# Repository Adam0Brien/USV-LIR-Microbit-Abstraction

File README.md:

# USV-LIR-Microbit-Abstraction
Final year project Applied Computing (IoT)

## Academic Title - "USV-Lir Micro: bit Sensor Pod Abstraction"

## Commercial Title - "Micro:Bit Sensor Pod breakout Board"
<br>

<br>

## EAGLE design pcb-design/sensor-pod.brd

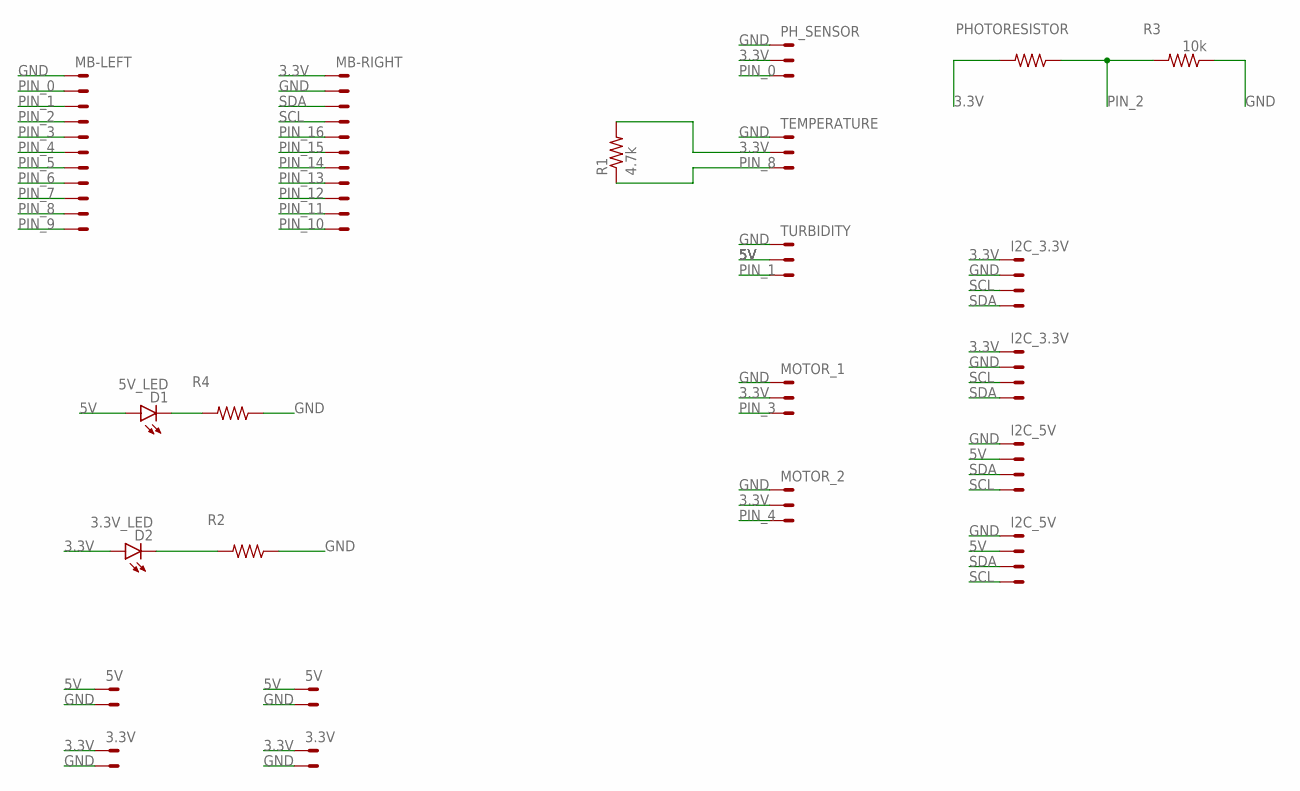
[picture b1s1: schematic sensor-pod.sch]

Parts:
1: 5V; 22-23-2021
D1: 5V_LED; SFH482
D2: 3.3V_LED; SFH482
PHOTORESISTOR: R-US_0204/7; 0204/7
R1: 4.7k; 0204/7
R2, R4: R-US_0204/7; 0204/7
R3: 10k; 0204/7
X1: PH_SENSOR; 22-23-2031
X2, X10: I2C_5V; 22-23-2041
X3: TURBIDITY; 22-23-2031
X4: 5V; 22-23-2021
X5: TEMPERATURE; 22-23-2031
X6: MOTOR_1; 22-23-2031
X7: MOTOR_2; 22-23-2031
X8, X9: I2C_3.3V; 22-23-2041
X11, X12: 3.3V; 22-23-2021
X15: MB-LEFT; 22-23-2111
X16: MB-RIGHT; 22-23-2111

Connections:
3.3V: D2.A, PHOTORESISTOR.2, R1.2, X1.2, X5.2, X6.2, X7.2, X8.1, X9.1, X11.1, X12.1, X16.1
5V: 1.1, D1.A, X2.2, X3.2, X4.1, X10.2
GND: 1.2, R2.1, R3.1, R4.1, X1.1, X2.1, X3.1, X4.2, X5.1, X6.1, X7.1, X8.2, X9.2, X10.1, X11.2, X12.2, X15.1, X16.2
unnamed: D1.K (C), R4.2
unnamed: D2.K (C), R2.2
PIN_0: X1.3, X15.2
PIN_1: X3.3, X15.3
PIN_2: PHOTORESISTOR.1, R3.2, X15.4
PIN_3: X6.3, X15.5
PIN_4: X7.3, X15.6
PIN_5: X15.7
PIN_6: X15.8
PIN_7: X15.9
PIN_8: R1.1, X5.3, X15.10
PIN_9: X15.11
PIN_10: X16.11
PIN_11: X16.10
PIN_12: X16.9
PIN_13: X16.8
PIN_14: X16.7
PIN_15: X16.6
PIN_16: X16.5
SCL: X2.4, X8.3, X9.3, X10.4, X16.4
SDA: X2.3, X8.4, X9.4, X10.3, X16.3

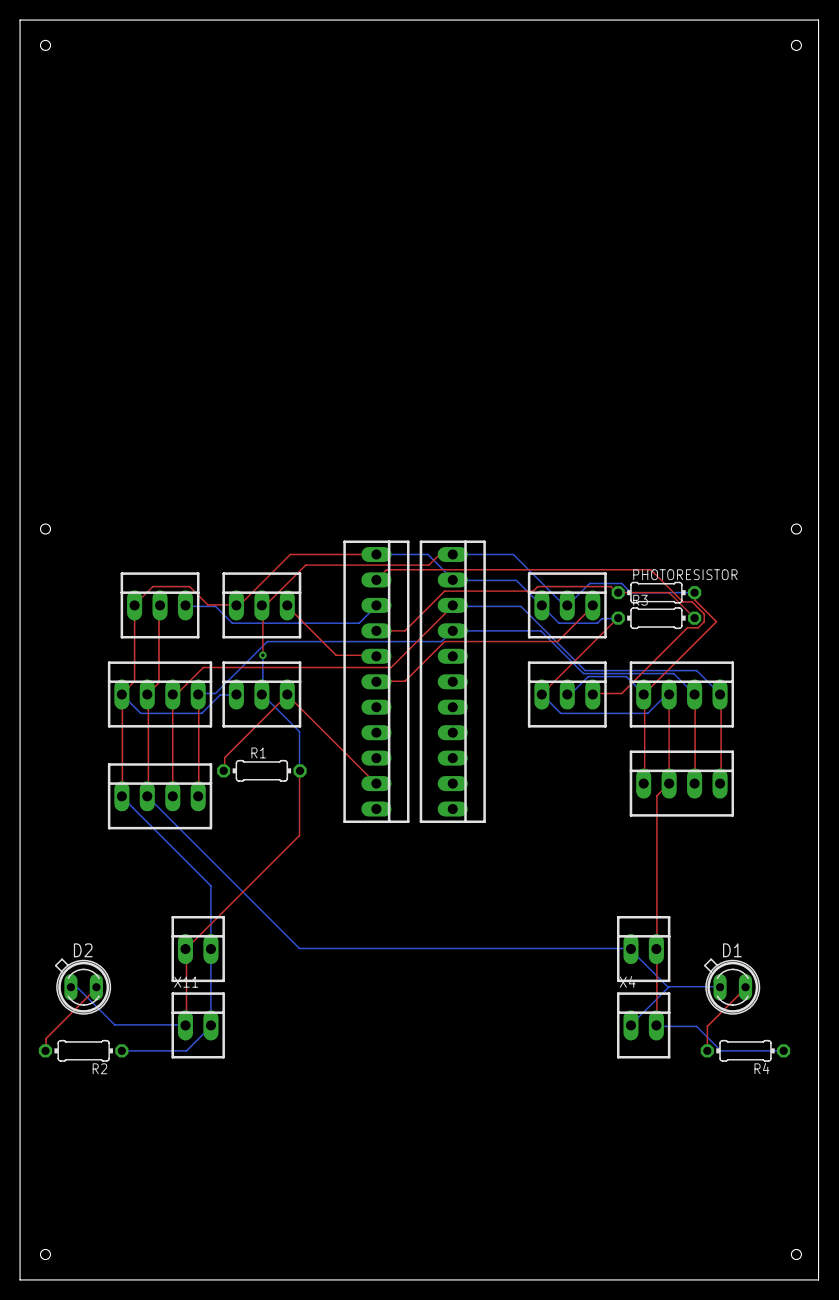
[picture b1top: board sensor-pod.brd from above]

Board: 2 copper layers, 79.7 x 125.7 mm, 22 parts (0 on the bottom side), 13 nets.

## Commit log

2023-12-21 Added cardboard hoverbit reciever code
2023-12-21 Added cardboard hoverbit transmitter code
2023-12-21 Added basic implementation of a USV microbit library
2024-01-05 Added project description
2024-01-17 pcb-design: Added initial PCB design for sensor pod
2024-01-17 pcb-design: Added pcb.md along with screenshots of design
2024-01-18 pcb-design/pcb.md: Correct image file extention
2024-01-18 pcb-design: Changed board layout and assigned pins for sensors.
2024-01-23 Added Temperature sensor code.
2024-01-29 Sensor pod: Fix temp sensor code to use P8 + Changed PCB to match
2024-01-29 Updated pcb schematic
2024-01-31 feat: Added pH sensor script
2024-02-01 Add Project website to github pages
2024-02-01 Sensor pod: Added pH sensor script
2024-02-06 pcb-design: Draft 2 Added LDR and power LED's + Changed board size/placement
2024-02-08 sensor-scripts: Added LDR code that interfaces with LCD
2024-02-11 pcd-design: Decreased distance between components and microbit interface. Increased PCB size.
2024-02-19 Sensor-pod local temp test.
2024-02-20 feat: temp,ph,lcd demo working
2024-02-21 MicroBit Library: Added Temp, pH and local display makeblocks.
2024-02-29 feat: Added makeblock for LDR reading
2024-02-29 feat: Added temperature sensor dependancies from microbit-dstemp
2024-03-01 docs: Added getting started docs page, renamed main.ts to sensorPod.ts
2024-03-01 Delete microbit-usv-lib directory
    Removed old Micro: bit Sensor pod library,
    Newest version is located in sensor-pod/sensorPod.ts
2024-03-07 docs: Added hardware section
2024-03-07 docs: Added MQTT-Design-Pattern.md
2024-03-07 Moved: pcb-design/pcb.md -> docs/pcb.md
2024-03-07 docs/hardware.md: Update Microbit pin connections
2024-03-07 Added USV Library
2024-03-11 Added issue templates
2024-03-15 3D-Prints: Added sensor pod bracket
2024-03-15 feat: Added sensor deployment mechanism to USV-API.
2024-03-19 USV/feat: Added Makecode blocks for Motor Control
2024-03-20 USV: Refactor code for better readability
2024-03-28 Update: img/poster.png
2024-04-02 Fix: Sensor deploy triggering unexpectedly
2024-04-02 feat: Added Sensor Pod to USV Comms.
2024-04-02 Feat: Add sensor pod Auto Drive
2024-04-03 fix: USV/USV.ts adjust left motor code to account for CCW motor
2024-04-04 feat: Added Listen for sensor pod data block
2024-04-04 feat: Added Sensor-Pod to Beebotte Cloud
2024-04-04 Added Makecode link to USV-User.ts
2024-04-04 docs: Update MQTT-Design-Pattern.md
2024-04-06 USV-Cloud: Update docs, Added IFTTT + App sensor deploy
2024-04-11 USV: Added Manual motor control block + Added default time values
2024-04-16 3D Print Files: Added 3D Print files for Sensor pod
2024-04-16 nit: Ignore gcode from repo language statistics
2024-04-21 USV: Added Radio arming to Startup blocks, Updated Auto Drive block to take speed as input
2024-04-24 USV: Changed USV Sensor deploy and USV-Mode to Radio Recieved String/Number
2024-04-24 USV: Remove local Arm for radio Arm
2024-06-11 USV/Updated OnBoard.ts
    Fixed Auto Drive logic
